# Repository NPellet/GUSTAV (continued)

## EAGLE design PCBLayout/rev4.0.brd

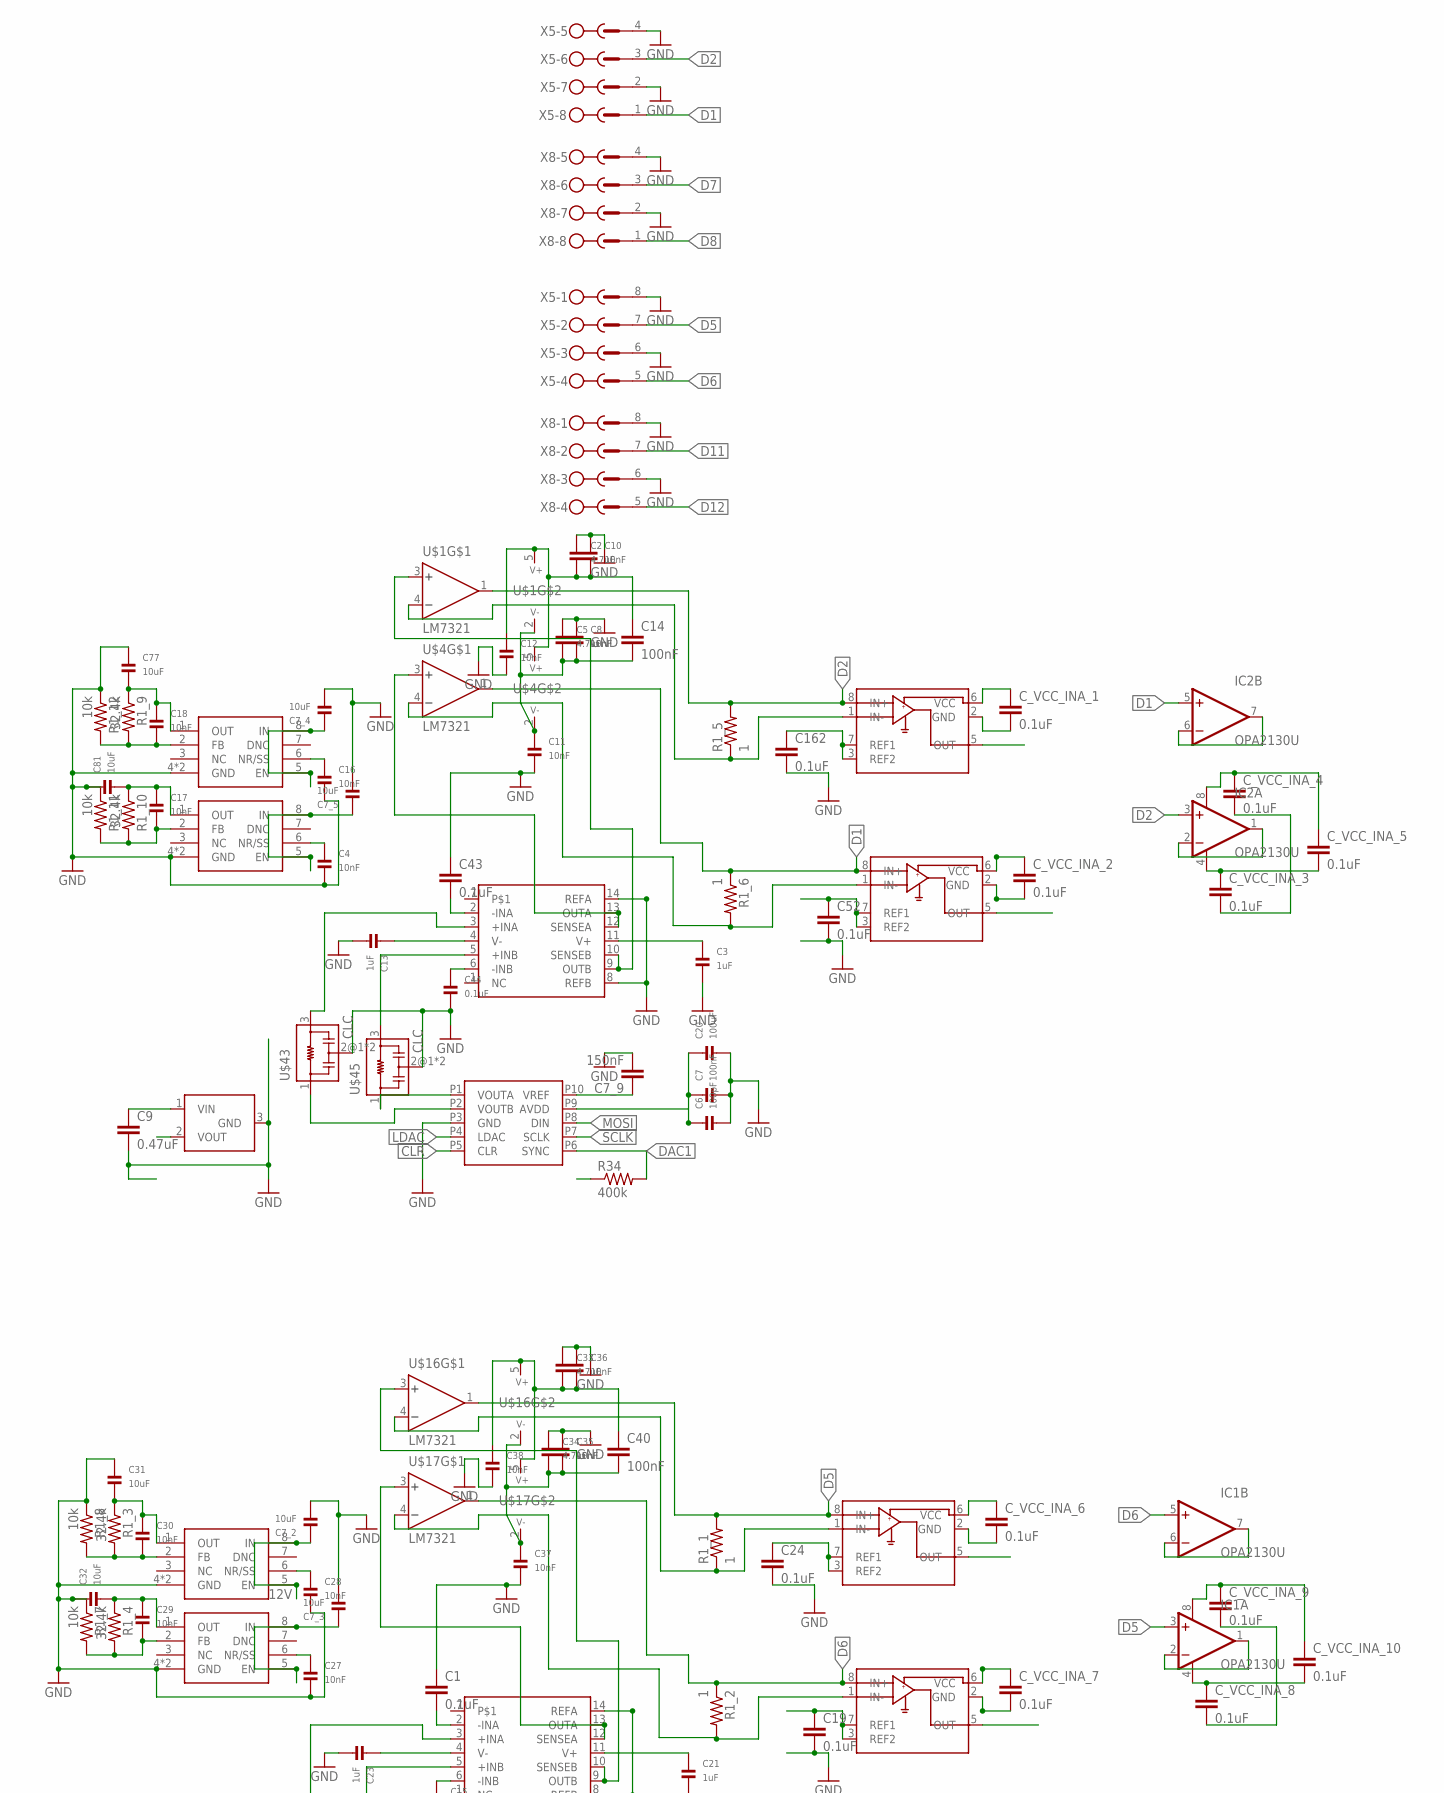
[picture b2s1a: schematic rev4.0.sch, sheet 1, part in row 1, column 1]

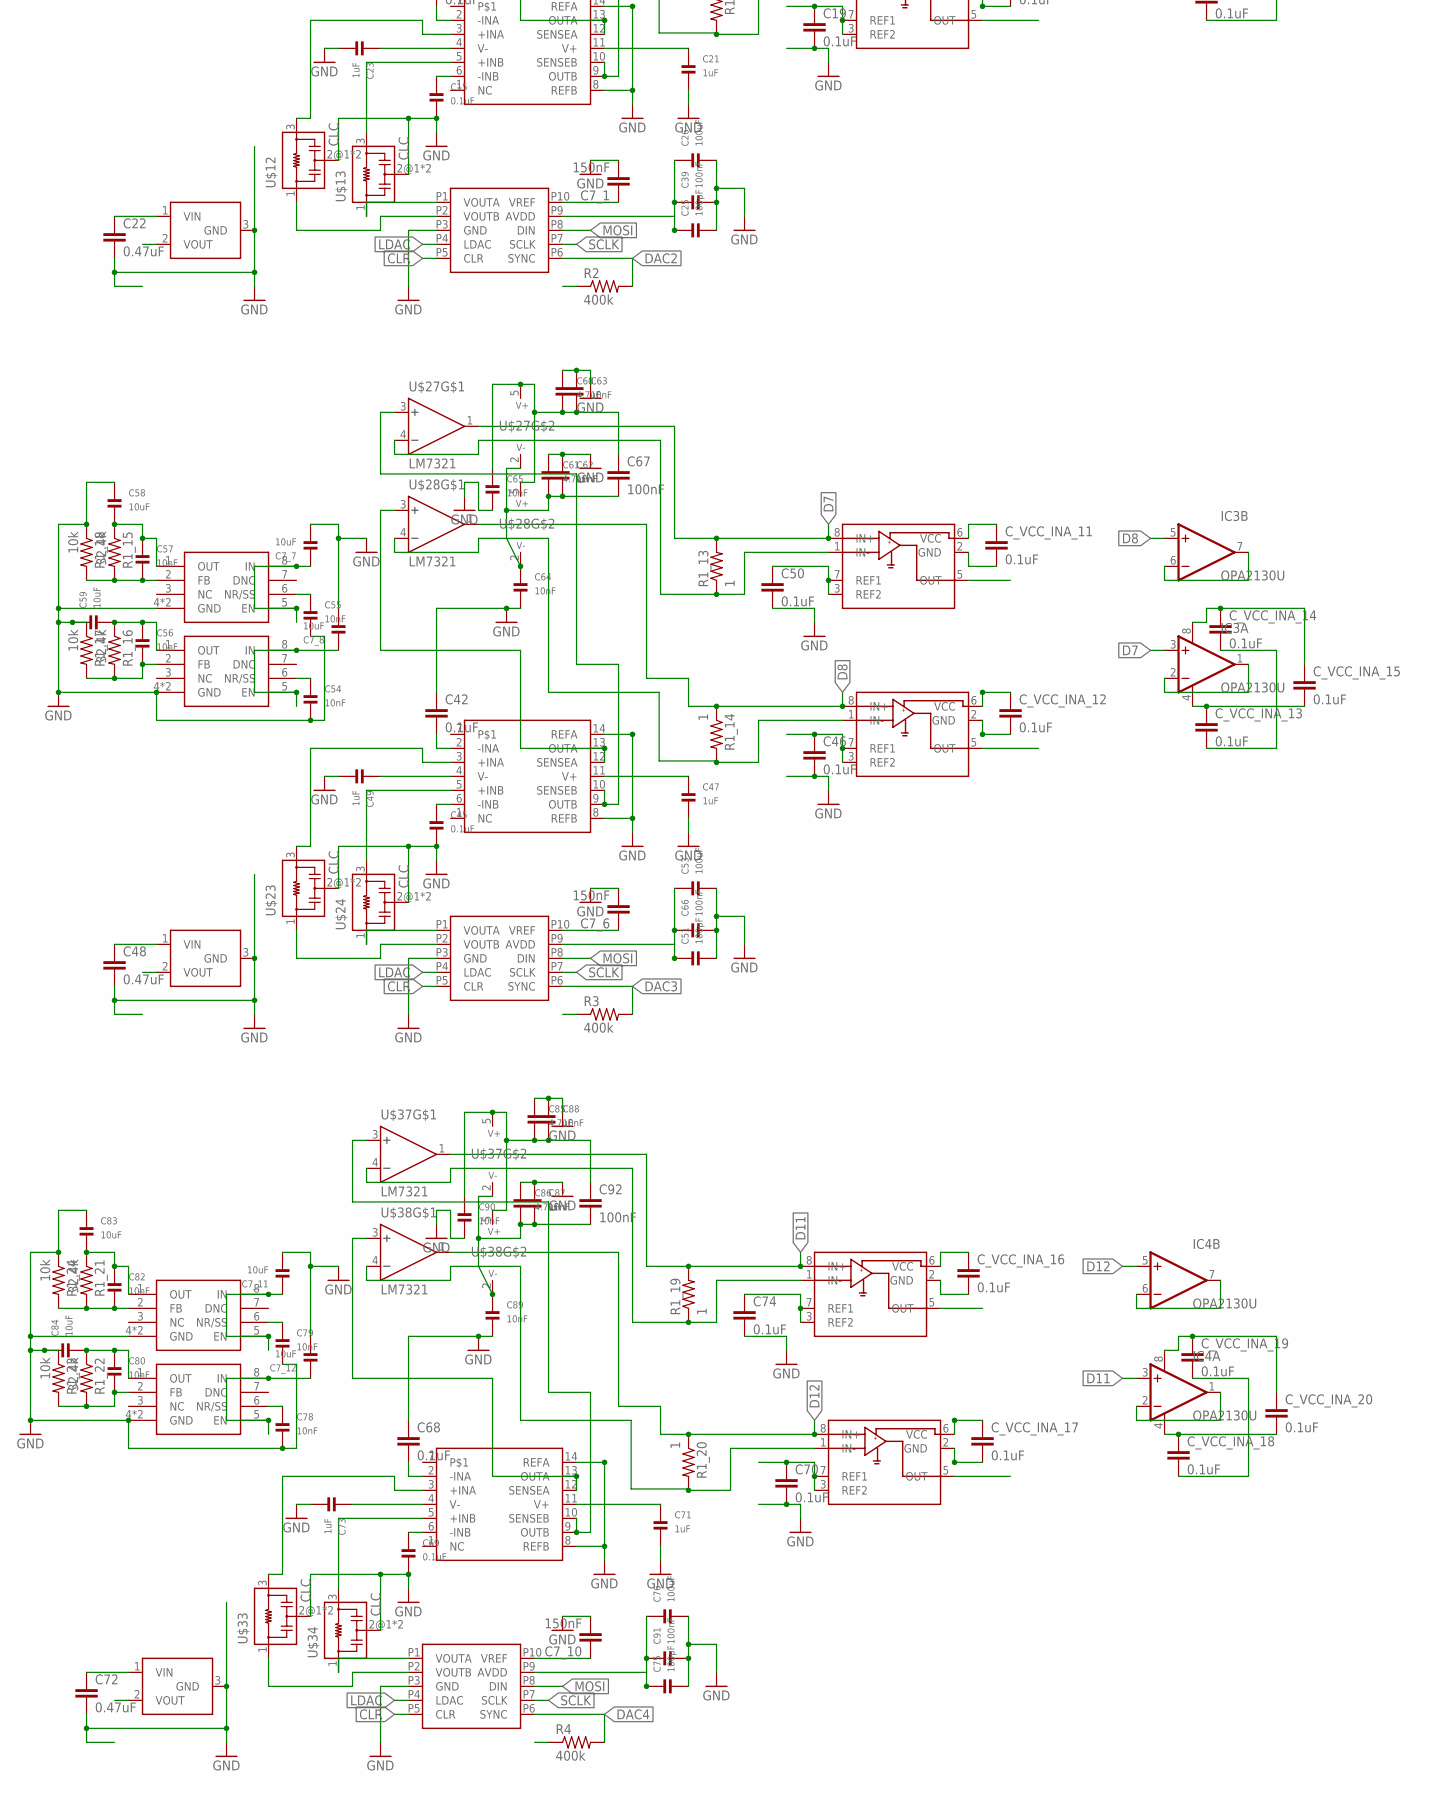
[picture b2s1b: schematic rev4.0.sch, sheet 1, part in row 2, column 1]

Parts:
C1, C19, C24, C42, C43, C46, C50, C52, C68, C70, C74, C162: 0.1uF; 0402-CAP
C2, C5, C33, C34, C60, C61, C85, C86: 4.7uF; 0805
C3, C13, C21, C23, C47, C49, C71, C73: 1uF; 0402
C4, C8, C10, C11, C12, C16, C17, C18, C27, C28, C29, C30, C35, C36, C37, C38, C54, C55, C56, C57, C62, C63, C64, C65, C78, C79, C80, C82, C87, C88, C89, C90: 10nF; 0402
C6, C25, C51, C75: 100pF; 0402
C7, C39, C66, C91: 100nF; 0402
C7_1, C7_6, C7_9, C7_10: 150nF; 0402-CAP
C7_2, C7_3, C7_4, C7_5, C7_7, C7_8, C7_11, C7_12, C31, C32, C58, C59, C77, C81, C83, C84: 10uF; 0805
C9, C22, C48, C72: 0.47uF; 0402-CAP
C14, C40, C67, C92: 100nF; 0402-CAP
C15, C44, C45, C69: 0.1uF; 0402
C20, C26, C53, C76: 100uF; 1206
C_VCC_INA_1, C_VCC_INA_2, C_VCC_INA_3, C_VCC_INA_4, C_VCC_INA_5, C_VCC_INA_6, C_VCC_INA_7, C_VCC_INA_8, C_VCC_INA_9, C_VCC_INA_10, C_VCC_INA_11, C_VCC_INA_12, C_VCC_INA_13, C_VCC_INA_14, C_VCC_INA_15, C_VCC_INA_16, C_VCC_INA_17, C_VCC_INA_18, C_VCC_INA_19, C_VCC_INA_20: 0.1uF; 0402-CAP
IC1, IC2, IC3, IC4: OPA2130U; SO08
R1_1, R1_2, R1_5, R1_6, R1_13, R1_14, R1_19, R1_20: 1; 0603-RES
R1_3, R1_4, R1_9, R1_10, R1_15, R1_16, R1_21, R1_22: 32.4k; 0603-RES
R1_7, R1_8, R1_11, R1_12, R1_17, R1_18, R1_23, R1_24: 10k; 0603-RES
R2, R3, R4, R34: 400k; 0603-RES
REF1, REF2, REF3, REF3040: REF3040; DBZ_R-PDSO-G3
U$1, U$4, U$16, U$17, U$27, U$28, U$37, U$38: LM7321; DCK_R-PDSO-G5
U$2, U$10, U$20, U$31: INA2132; SO-14
U$3, U$11, U$21, U$32: DAC7563; S-PDSO-G10
U$5, U$7, U$8, U$9, U$18, U$19, U$29, U$30: INA285PDSO-G8; S-PDSO-G08-NOTHERMALPAD
U$12, U$13, U$23, U$24, U$33, U$34, U$43, U$45: CLC; NFM21C
U$14, U$15, U$25, U$26, U$35, U$36, U$53, U$54: TPS7A30; S-PDSO-G08
X5, X8: MSTBV8

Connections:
12V: C7_2.1, C7_4.1, C7_7.1, C7_11.1, U$14.5 (EN), U$14.8 (IN), U$25.5 (EN), U$25.8 (IN), U$35.5 (EN), U$35.8 (IN), U$53.5 (EN), U$53.8 (IN); also elsewhere on the board
-9V: C7_3.1, C7_5.1, C7_8.1, C7_12.1, U$15.5 (EN), U$15.8 (IN), U$26.5 (EN), U$26.8 (IN), U$36.5 (EN), U$36.8 (IN), U$54.5 (EN), U$54.8 (IN); also elsewhere on the board
CLR: U$3.P5 (CLR), U$11.P5 (CLR), U$21.P5 (CLR), U$32.P5 (CLR); also elsewhere on the board
D1: IC2.5 (+IN), R1_6.1, U$4.1 (OUT), U$8.8 (IN+), X5.1
D2: IC2.3 (+IN), R1_5.2, U$1.1 (OUT), U$7.8 (IN+), X5.3
D5: IC1.3 (+IN), R1_1.2, U$5.8 (IN+), U$16.1 (OUT), X5.7
D6: IC1.5 (+IN), R1_2.1, U$9.8 (IN+), U$17.1 (OUT), X5.5
D7: IC3.3 (+IN), R1_13.2, U$18.8 (IN+), U$27.1 (OUT), X8.3
D8: IC3.5 (+IN), R1_14.1, U$19.8 (IN+), U$28.1 (OUT), X8.1
D11: IC4.3 (+IN), R1_19.2, U$29.8 (IN+), U$37.1 (OUT), X8.7
D12: IC4.5 (+IN), R1_20.1, U$30.8 (IN+), U$38.1 (OUT), X8.5
DAC1: R34.2, U$3.P6 (SYNC); also elsewhere on the board
DAC2: R2.2, U$11.P6 (SYNC); also elsewhere on the board
DAC3: R3.2, U$21.P6 (SYNC); also elsewhere on the board
DAC4: R4.2, U$32.P6 (SYNC); also elsewhere on the board
GND: C1.1, C2.1, C3.2, C4.2, C5.1, C6.2, C7.2, C7_1.2, C7_2.2, C7_3.2, C7_4.2, C7_5.2, C7_6.2, C7_7.2, C7_8.2, C7_9.2, C7_10.2, C7_11.2, C7_12.2, C8.1, C9.2, C10.1, C11.2, C12.2, C13.2, C15.2, C16.2, C19.2, C20.2, C21.2, C22.2, C23.2, C24.2, C25.2, C26.2, C27.2, C28.2, C31.1, C32.1, C33.1, C34.1, C35.1, C36.1, C37.2, C38.2, C39.2, C42.1, C43.1, C44.2, C45.2, C46.2, C47.2, C48.2, C49.2, C50.2, C51.2, C52.2, C53.2, C54.2, C55.2, C58.1, C59.1, C60.1, C61.1, C62.1, C63.1, C64.2, C65.2, C66.2, C68.1, C69.2, C70.2, C71.2, C72.2, C73.2, C74.2, C75.2, C76.2, C77.1, C78.2, C79.2, C81.1, C83.1, C84.1, C85.1, C86.1, C87.1, C88.1, C89.2, C90.2, C91.2, C162.2, C_VCC_INA_1.2, C_VCC_INA_2.2, C_VCC_INA_3.2, C_VCC_INA_4.2, C_VCC_INA_6.2, C_VCC_INA_7.2, C_VCC_INA_8.2, C_VCC_INA_9.2, C_VCC_INA_11.2, C_VCC_INA_12.2, C_VCC_INA_13.2, C_VCC_INA_14.2, C_VCC_INA_16.2, C_VCC_INA_17.2, C_VCC_INA_18.2, C_VCC_INA_19.2, R1_7.1, R1_8.1, R1_11.1, R1_12.1, R1_17.1, R1_18.1, R1_23.1, R1_24.1, REF1.3 (GND), REF2.3 (GND), REF3.3 (GND), REF3040.3 (GND), U$2.8 (REFB), U$2.14 (REFA), U$3.P3 (GND), U$5.2 (GND), U$7.2 (GND), U$8.2 (GND), U$9.2 (GND), U$10.8 (REFB), U$10.14 (REFA), U$11.P3 (GND), U$12.2@1 (2), U$12.2@2 (2), U$13.2@1 (2), U$13.2@2 (2), U$14.4 (GND), U$14.TH (GND), U$15.4 (GND), U$15.TH (GND), U$18.2 (GND), U$19.2 (GND), U$20.8 (REFB), U$20.14 (REFA), U$21.P3 (GND), U$23.2@1 (2), U$23.2@2 (2), U$24.2@1 (2), U$24.2@2 (2), U$25.4 (GND), U$25.TH (GND), U$26.4 (GND), U$26.TH (GND), U$29.2 (GND), U$30.2 (GND), U$31.8 (REFB), U$31.14 (REFA), U$32.P3 (GND), U$33.2@1 (2), U$33.2@2 (2), U$34.2@1 (2), U$34.2@2 (2), U$35.4 (GND), U$35.TH (GND), U$36.4 (GND), U$36.TH (GND), U$43.2@1 (2), U$43.2@2 (2), U$45.2@1 (2), U$45.2@2 (2), U$53.4 (GND), U$53.TH (GND), U$54.4 (GND), U$54.TH (GND), X5.2, X5.4, X5.6, X5.8, X8.2, X8.4, X8.6, X8.8; also elsewhere on the board
LDAC: U$3.P4 (LDAC), U$11.P4 (LDAC), U$21.P4 (LDAC), U$32.P4 (LDAC); also elsewhere on the board
MOSI: U$3.P8 (DIN), U$11.P8 (DIN), U$21.P8 (DIN), U$32.P8 (DIN); also elsewhere on the board
MUX1: IC2.6 (-IN), IC2.7 (OUT); also elsewhere on the board
MUX2: IC2.1 (OUT), IC2.2 (-IN); also elsewhere on the board
MUX3: IC1.6 (-IN), IC1.7 (OUT); also elsewhere on the board
MUX4: IC1.1 (OUT), IC1.2 (-IN); also elsewhere on the board
MUX5: IC3.6 (-IN), IC3.7 (OUT); also elsewhere on the board
MUX6: IC3.1 (OUT), IC3.2 (-IN); also elsewhere on the board
MUX7: IC4.6 (-IN), IC4.7 (OUT); also elsewhere on the board
MUX8: IC4.1 (OUT), IC4.2 (-IN); also elsewhere on the board
MUX9: U$7.5 (OUT); also elsewhere on the board
MUX10: U$8.5 (OUT); also elsewhere on the board
MUX11: U$5.5 (OUT); also elsewhere on the board
MUX12: U$9.5 (OUT); also elsewhere on the board
MUX13: U$18.5 (OUT); also elsewhere on the board
MUX14: U$19.5 (OUT); also elsewhere on the board
MUX15: U$29.5 (OUT); also elsewhere on the board
MUX16: U$30.5 (OUT); also elsewhere on the board
unnamed: U$3.P1 (VOUTA), U$45.1
unnamed: U$1.3 (+), U$2.9 (OUTB), U$2.10 (SENSEB)
unnamed: U$3.P2 (VOUTB), U$43.1
unnamed: U$2.12 (SENSEA), U$2.13 (OUTA), U$4.3 (+)
unnamed: U$10.9 (OUTB), U$10.10 (SENSEB), U$16.3 (+)
unnamed: U$10.12 (SENSEA), U$10.13 (OUTA), U$17.3 (+)
unnamed: U$10.5 (+INB), U$13.3
unnamed: C27.1, U$15.6 (NR/SS)
unnamed: C28.1, U$14.6 (NR/SS)
unnamed: C29.2, R1_4.2, R1_7.2, U$15.2 (FB)
unnamed: C30.2, R1_3.2, R1_8.2, U$14.2 (FB)
unnamed: U$11.P1 (VOUTA), U$13.1
unnamed: U$11.P2 (VOUTB), U$12.1
unnamed: U$20.9 (OUTB), U$20.10 (SENSEB), U$27.3 (+)
unnamed: U$20.12 (SENSEA), U$20.13 (OUTA), U$28.3 (+)
unnamed: U$20.5 (+INB), U$24.3
unnamed: C54.1, U$26.6 (NR/SS)
unnamed: C55.1, U$25.6 (NR/SS)
unnamed: C56.2, R1_16.2, R1_17.2, U$26.2 (FB)
unnamed: C57.2, R1_15.2, R1_18.2, U$25.2 (FB)
unnamed: U$21.P1 (VOUTA), U$24.1
unnamed: U$21.P2 (VOUTB), U$23.1
unnamed: U$31.9 (OUTB), U$31.10 (SENSEB), U$37.3 (+)
unnamed: U$31.12 (SENSEA), U$31.13 (OUTA), U$38.3 (+)
unnamed: U$31.5 (+INB), U$34.3
unnamed: C78.1, U$36.6 (NR/SS)
unnamed: C79.1, U$35.6 (NR/SS)
unnamed: C80.2, R1_22.2, R1_23.2, U$36.2 (FB)
unnamed: C82.2, R1_21.2, R1_24.2, U$35.2 (FB)
unnamed: U$32.P1 (VOUTA), U$34.1
unnamed: U$32.P2 (VOUTB), U$33.1
unnamed: U$2.5 (+INB), U$45.3
unnamed: C4.1, U$54.6 (NR/SS)
unnamed: C16.1, U$53.6 (NR/SS)
unnamed: C17.2, R1_10.2, R1_11.2, U$54.2 (FB)
unnamed: C18.2, R1_9.2, R1_12.2, U$53.2 (FB)
OUTPUTA: R1_6.2, U$4.4 (-), U$8.1 (IN-)
OUTPUTA1: R1_2.2, U$9.1 (IN-), U$17.4 (-)
OUTPUTA2: R1_14.2, U$19.1 (IN-), U$28.4 (-)
OUTPUTA3: R1_20.2, U$30.1 (IN-), U$38.4 (-)
OUTPUTB: R1_5.1, U$1.4 (-), U$7.1 (IN-)
OUTPUTB1: R1_1.1, U$5.1 (IN-), U$16.4 (-)
OUTPUTB2: R1_13.1, U$18.1 (IN-), U$27.4 (-)
OUTPUTB3: R1_19.1, U$29.1 (IN-), U$37.4 (-)
REF2: C1.2, C15.1, C19.1, C24.1, C42.2, C43.2, C44.1, C45.1, C46.1, C50.1, C52.1, C68.2, C69.1, C70.1, C74.1, C162.1, U$2.2 (-INA), U$2.6 (-INB), U$5.3 (REF2), U$5.7 (REF1), U$7.3 (REF2), U$7.7 (REF1), U$8.3 (REF2), U$8.7 (REF1), U$9.3 (REF2), U$9.7 (REF1), U$10.2 (-INA), U$10.6 (-INB), U$18.3 (REF2), U$18.7 (REF1), U$19.3 (REF2), U$19.7 (REF1), U$20.2 (-INA), U$20.6 (-INB), U$29.3 (REF2), U$29.7 (REF1), U$30.3 (REF2), U$30.7 (REF1), U$31.2 (-INA), U$31.6 (-INB); also elsewhere on the board
REF3: C7_1.1, REF1.2 (VOUT), U$11.P10 (VREF)
REF4: C7_9.1, REF3040.2 (VOUT), U$3.P10 (VREF)
REF6: C7_6.1, REF2.2 (VOUT), U$21.P10 (VREF)
REF8: C7_10.1, REF3.2 (VOUT), U$32.P10 (VREF)
SCLK: U$3.P7 (SCLK), U$11.P7 (SCLK), U$21.P7 (SCLK), U$32.P7 (SCLK); also elsewhere on the board
VOUTA: U$2.3 (+INA), U$43.3
VOUTA1: U$10.3 (+INA), U$12.3
VOUTA2: U$20.3 (+INA), U$23.3
VOUTA3: U$31.3 (+INA), U$33.3
VREF: C2.2, C3.1, C6.1, C7.1, C9.1, C10.2, C12.1, C14.1, C18.1, C20.1, C77.2, C_VCC_INA_1.1, C_VCC_INA_2.1, C_VCC_INA_4.1, C_VCC_INA_5.1, IC2.8 (V+), R1_9.1, R34.1, REF3040.1 (VIN), U$1.5 (V+), U$2.11 (V+), U$3.P9 (AVDD), U$4.5 (V+), U$7.6 (VCC), U$8.6 (VCC), U$53.1 (OUT)
VREF1: C21.1, C22.1, C25.1, C26.1, C30.1, C31.2, C33.2, C36.2, C38.1, C39.1, C40.1, C_VCC_INA_6.1, C_VCC_INA_7.1, C_VCC_INA_9.1, C_VCC_INA_10.1, IC1.8 (V+), R1_3.1, R2.1, REF1.1 (VIN), U$5.6 (VCC), U$9.6 (VCC), U$10.11 (V+), U$11.P9 (AVDD), U$14.1 (OUT), U$16.5 (V+), U$17.5 (V+)
VREF2: C47.1, C48.1, C51.1, C53.1, C57.1, C58.2, C60.2, C63.2, C65.1, C66.1, C67.1, C_VCC_INA_11.1, C_VCC_INA_12.1, C_VCC_INA_14.1, C_VCC_INA_15.1, IC3.8 (V+), R1_15.1, R3.1, REF2.1 (VIN), U$18.6 (VCC), U$19.6 (VCC), U$20.11 (V+), U$21.P9 (AVDD), U$25.1 (OUT), U$27.5 (V+), U$28.5 (V+)
VREF3: C71.1, C72.1, C75.1, C76.1, C82.1, C83.2, C85.2, C88.2, C90.1, C91.1, C92.1, C_VCC_INA_16.1, C_VCC_INA_17.1, C_VCC_INA_19.1, C_VCC_INA_20.1, IC4.8 (V+), R1_21.1, R4.1, REF3.1 (VIN), U$29.6 (VCC), U$30.6 (VCC), U$31.11 (V+), U$32.P9 (AVDD), U$35.1 (OUT), U$37.5 (V+), U$38.5 (V+)
VREF-: C5.2, C8.2, C11.1, C13.1, C14.2, C17.1, C81.2, C_VCC_INA_3.1, C_VCC_INA_5.2, IC2.4 (V-), R1_10.1, U$1.2 (V-), U$2.4 (V-), U$4.2 (V-), U$54.1 (OUT)
VREF-1: C23.1, C29.1, C32.2, C34.2, C35.2, C37.1, C40.2, C_VCC_INA_8.1, C_VCC_INA_10.2, IC1.4 (V-), R1_4.1, U$10.4 (V-), U$15.1 (OUT), U$16.2 (V-), U$17.2 (V-)
VREF-2: C49.1, C56.1, C59.2, C61.2, C62.2, C64.1, C67.2, C_VCC_INA_13.1, C_VCC_INA_15.2, IC3.4 (V-), R1_16.1, U$20.4 (V-), U$26.1 (OUT), U$27.2 (V-), U$28.2 (V-)
VREF-3: C73.1, C80.1, C84.2, C86.2, C87.2, C89.1, C92.2, C_VCC_INA_18.1, C_VCC_INA_20.2, IC4.4 (V-), R1_22.1, U$31.4 (V-), U$36.1 (OUT), U$37.2 (V-), U$38.2 (V-)

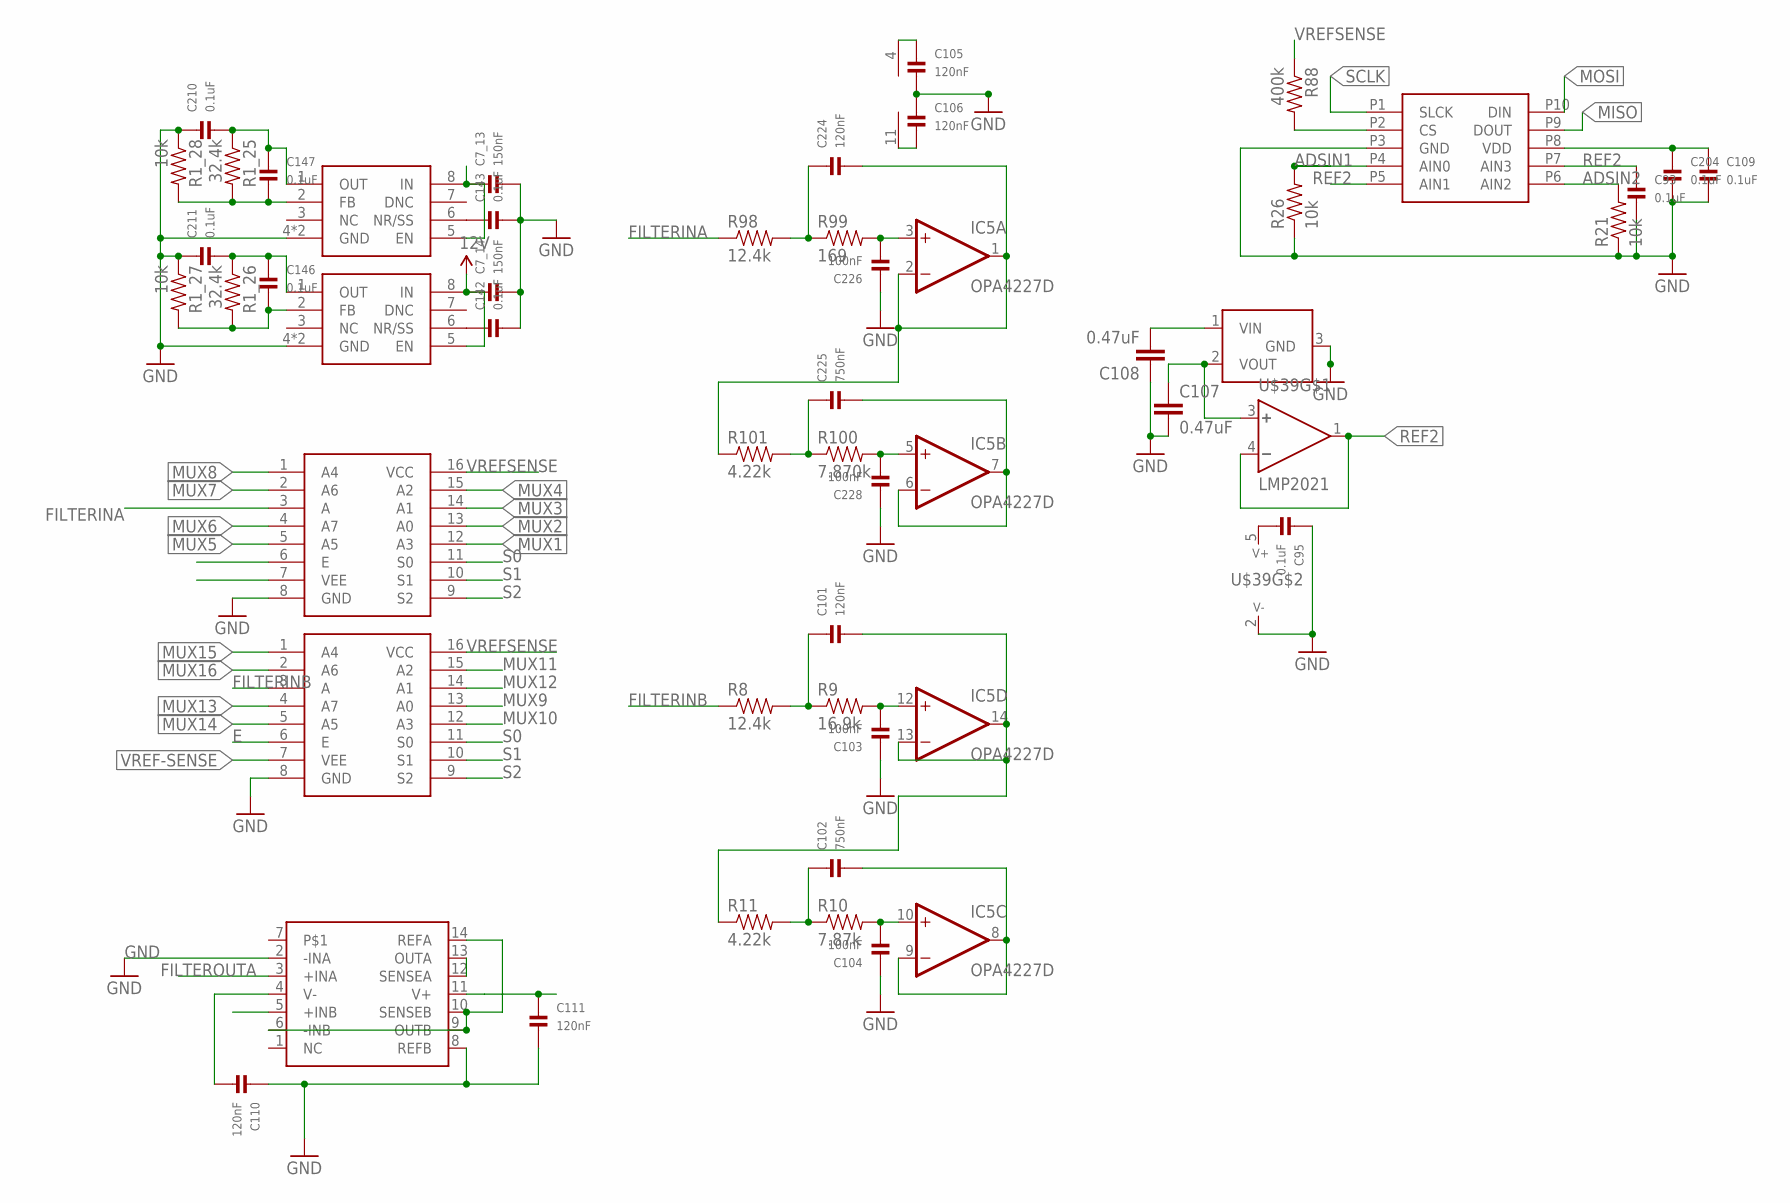
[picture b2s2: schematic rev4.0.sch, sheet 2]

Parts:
C7_13, C7_14: 150nF; 0603-MINI
C93, C95, C109, C142, C143, C146, C147, C204: 0.1uF; 0402
C101, C105, C106, C110, C111, C224: 120nF; 0402
C102, C225: 750nF; 0402
C103, C104, C226, C228: 100nF; 0402
C107, C108: 0.47uF; 0402-CAP
C210, C211: 0.1uF; 0603-MINI
IC5: OPA4227D; SO14
R1_25, R1_26: 32.4k; 0603-RES
R1_27, R1_28: 10k; 0603-RES
R8, R98: 12.4k; 0603-RES
R9: 16.9k; 0603-RES
R10: 7.87k; 0603-RES
R11, R101: 4.22k; 0603-RES
R21, R26: 10k; 0603
R88: 400k; 0603-RES
R99: 169; 0603-RES
R100: 7.870k; 0603-RES
REF7: REF3020; DBZ_R-PDSO-G3
U$6, U$57: CD54HC4051; PW_R-PDSO-G16
U$39: LMP2021; SOT23-DBV
U$40: ADS1018; S-PDSO-G10
U$48, U$49: TPS7A30; S-PDSO-G08
U$58: INA2132; SO-14

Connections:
12V: C7_14.1, U$49.5 (EN), U$49.8 (IN); also elsewhere on the board
-9V: C7_13.1, U$48.5 (EN), U$48.8 (IN); also elsewhere on the board
ADCCS: R88.2, U$40.P2 (CS); also elsewhere on the board
ADSIN1: C102.2, IC5.8 (OUT), IC5.9 (-IN), R26.2, U$40.P4 (AIN0)
ADSIN2: R21.2, U$40.P6 (AIN2), U$58.12 (SENSEA), U$58.13 (OUTA)
E: U$6.6 (E), U$57.6 (E); also elsewhere on the board
FILTERINA: R98.1, U$6.3 (A)
FILTERINB: R8.1, U$57.3 (A)
FILTEROUTA: C225.2, IC5.6 (-IN), IC5.7 (OUT), U$58.3 (+INA)
GND: C7_13.2, C7_14.2, C93.2, C95.1, C103.1, C104.1, C105.2, C106.1, C107.2, C108.1, C109.2, C110.1, C111.2, C142.2, C143.2, C204.2, C210.1, C211.1, C226.1, C228.1, R1_27.1, R1_28.1, R21.1, R26.1, REF7.3 (GND), U$6.8 (GND), U$39.2 (V-), U$40.P3 (GND), U$48.4 (GND), U$48.TH (GND), U$49.4 (GND), U$49.TH (GND), U$57.8 (GND), U$58.2 (-INA), U$58.8 (REFB); also elsewhere on the board
MISO: U$40.P9 (DOUT); also elsewhere on the board
MOSI: U$40.P10 (DIN); also elsewhere on the board
MUX1: U$6.12 (A3); also elsewhere on the board
MUX2: U$6.13 (A0); also elsewhere on the board
MUX3: U$6.14 (A1); also elsewhere on the board
MUX4: U$6.15 (A2); also elsewhere on the board
MUX5: U$6.5 (A5); also elsewhere on the board
MUX6: U$6.4 (A7); also elsewhere on the board
MUX7: U$6.2 (A6); also elsewhere on the board
MUX8: U$6.1 (A4); also elsewhere on the board
MUX9: U$57.13 (A0); also elsewhere on the board
MUX10: U$57.12 (A3); also elsewhere on the board
MUX11: U$57.15 (A2); also elsewhere on the board
MUX12: U$57.14 (A1); also elsewhere on the board
MUX13: U$57.4 (A7); also elsewhere on the board
MUX14: U$57.5 (A5); also elsewhere on the board
MUX15: U$57.1 (A4); also elsewhere on the board
MUX16: U$57.2 (A6); also elsewhere on the board
unnamed: C107.1, REF7.2 (VOUT), U$39.3 (+)
unnamed: C101.2, IC5.13 (-IN), IC5.14 (OUT), R11.1
unnamed: C103.2, IC5.12 (+IN), R9.2
unnamed: C104.2, IC5.10 (+IN), R10.2
unnamed: C102.1, R10.1, R11.2
unnamed: U$58.6 (-INB), U$58.9 (OUTB), U$58.10 (SENSEB), U$58.14 (REFA)
unnamed: C101.1, R8.2, R9.1
unnamed: C143.1, U$48.6 (NR/SS)
unnamed: C142.1, U$49.6 (NR/SS)
unnamed: C146.2, R1_26.2, R1_27.2, U$49.2 (FB)
unnamed: C147.2, R1_25.2, R1_28.2, U$48.2 (FB)
unnamed: C226.2, IC5.3 (+IN), R99.2
unnamed: C228.2, IC5.5 (+IN), R100.2
unnamed: C225.1, R100.1, R101.2
unnamed: C224.2, IC5.1 (OUT), IC5.2 (-IN), R101.1
unnamed: C224.1, R98.2, R99.1
REF2: C93.1, U$39.1 (OUT), U$39.4 (-), U$40.P5 (AIN1), U$40.P7 (AIN3), U$58.5 (+INB); also elsewhere on the board
S0: U$6.11 (S0), U$57.11 (S0); also elsewhere on the board
S1: U$6.10 (S1), U$57.10 (S1); also elsewhere on the board
S2: U$6.9 (S2), U$57.9 (S2); also elsewhere on the board
SCLK: U$40.P1 (SLCK); also elsewhere on the board
VREF-SENSE: C106.2, C110.2, C147.1, C210.2, IC5.11 (V-), R1_25.1, U$6.7 (VEE), U$48.1 (OUT), U$57.7 (VEE), U$58.4 (V-)
VREFSENSE: C95.2, C105.1, C108.2, C109.1, C111.1, C146.1, C204.1, C211.2, IC5.4 (V+), R1_26.1, R88.1, REF7.1 (VIN), U$6.16 (VCC), U$39.5 (V+), U$40.P8 (VDD), U$49.1 (OUT), U$57.16 (VCC), U$58.11 (V+)

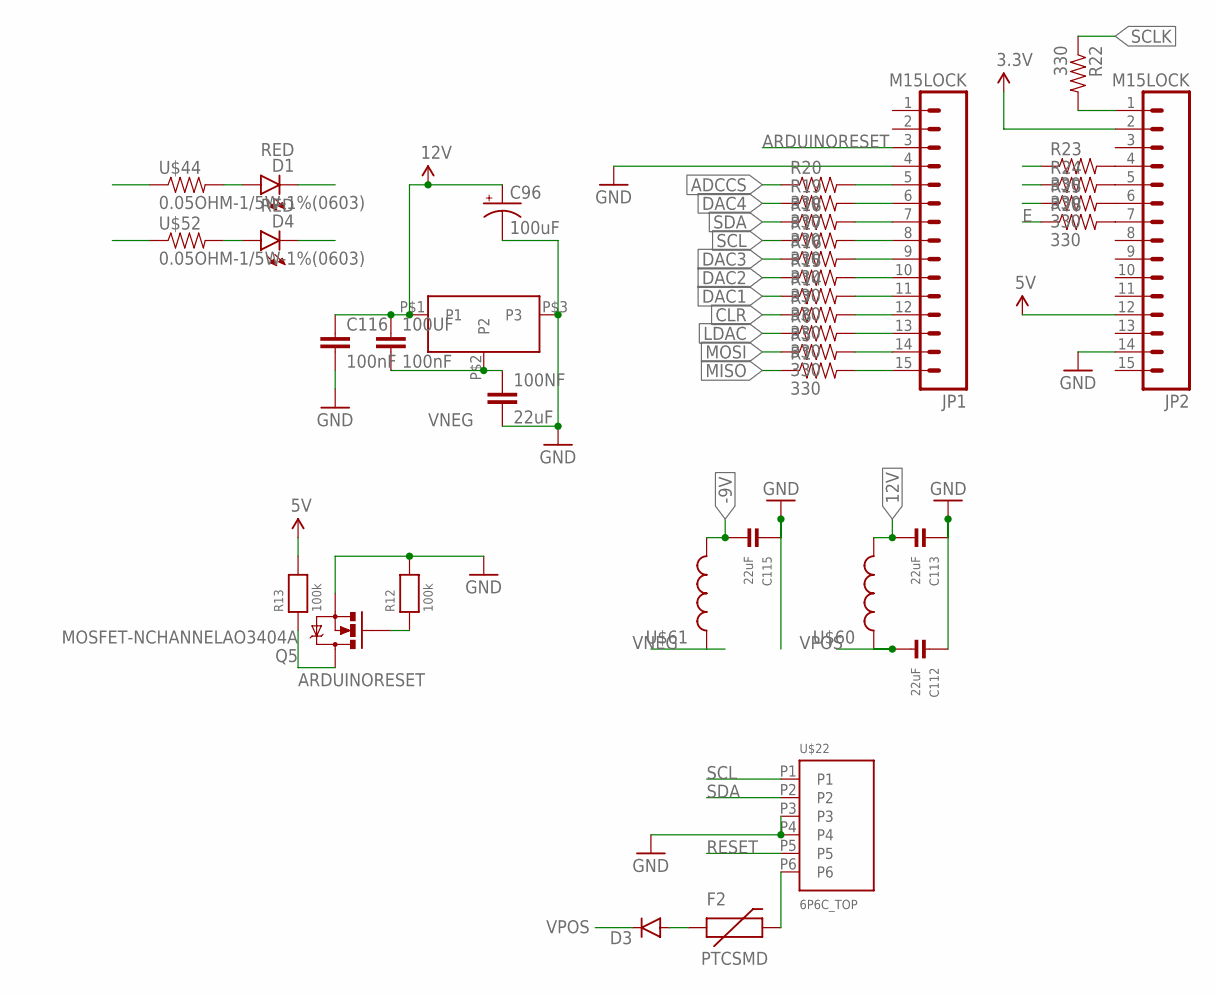
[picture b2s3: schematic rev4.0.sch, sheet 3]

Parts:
100NF: 22uF; 1206-CAP
100UF: 100nF; 1206-CAP
C96: 100uF; NIPPON_F80
C112, C113, C115: 22uF; 1206
C116: 100nF; 1206-CAP
D1, D4: RED; LED-1206
D3: DIODESMA; SMA-DIODE
F2: PTCSMD; PTC-1206
JP1, JP2: M15LOCK; 1X15_LOCK
Q5: MOSFET-NCHANNELAO3404A; SOT23-3
R1, R5, R6, R7, R14, R15, R16, R17, R18, R19, R20, R22, R23, R24, R25, R28: 330; 0603-RES
R12, R13: 100k; 0402
U$22: 6P6C_TOP
U$42: TSRN1
U$44, U$52: 0.05OHM-1/5W-1%(0603); 0603
U$60, U$61: INDUCTOR0603; 0603

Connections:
3.3V: JP2.2
5V: JP2.12, R13.2
12V: 100UF.1, C96.+, C113.2, C116.1, U$42.P$1 (P1), U$44.1, U$60.2; also elsewhere on the board
-9V: C115.2, D4.C, U$61.2; also elsewhere on the board
ADCCS: R20.1; also elsewhere on the board
ARDUINORESET: JP1.3, Q5.3 (D), R13.1
CLR: R7.1; also elsewhere on the board
D13: JP1.15, R1.2
D14: JP1.14, R5.2
D15: JP1.13, R6.2
D16: JP1.12, R7.2
D17: JP1.11, R14.2
D18: JP1.10, R15.2
D19: JP1.9, R16.2
D20: JP1.8, R17.2
D21: JP1.7, R18.2
D22: JP1.6, R19.2
D23: JP1.5, R20.2
DAC1: R14.1; also elsewhere on the board
DAC2: R15.1; also elsewhere on the board
DAC3: R16.1; also elsewhere on the board
DAC4: R19.1; also elsewhere on the board
E: R28.1; also elsewhere on the board
GND: 100NF.2, C96.-, C112.1, C113.1, C115.1, C116.2, D1.C, JP1.4, JP2.14, Q5.2 (S), R12.2, U$22.P3, U$22.P4, U$42.P$3 (P3), U$52.1; also elsewhere on the board
LDAC: R6.1; also elsewhere on the board
MISO: R1.1; also elsewhere on the board
MOSI: R5.1; also elsewhere on the board
unnamed: JP2.7, R28.2
unnamed: JP2.1, R22.2
unnamed: JP2.4, R23.2
unnamed: D1.A, U$44.2
unnamed: JP2.5, R24.2
unnamed: JP2.6, R25.2
unnamed: F2.2, U$22.P6
unnamed: D3.A, F2.1
unnamed: D4.A, U$52.2
RESET: Q5.1 (G), R12.1, U$22.P5
S0: R23.1; also elsewhere on the board
S1: R24.1; also elsewhere on the board
S2: R25.1; also elsewhere on the board
SCL: R17.1, U$22.P1
SCLK: R22.1; also elsewhere on the board
SDA: R18.1, U$22.P2
VNEG: 100NF.1, 100UF.2, U$42.P$2 (P2), U$61.1
VPOS: C112.2, D3.C, U$60.1

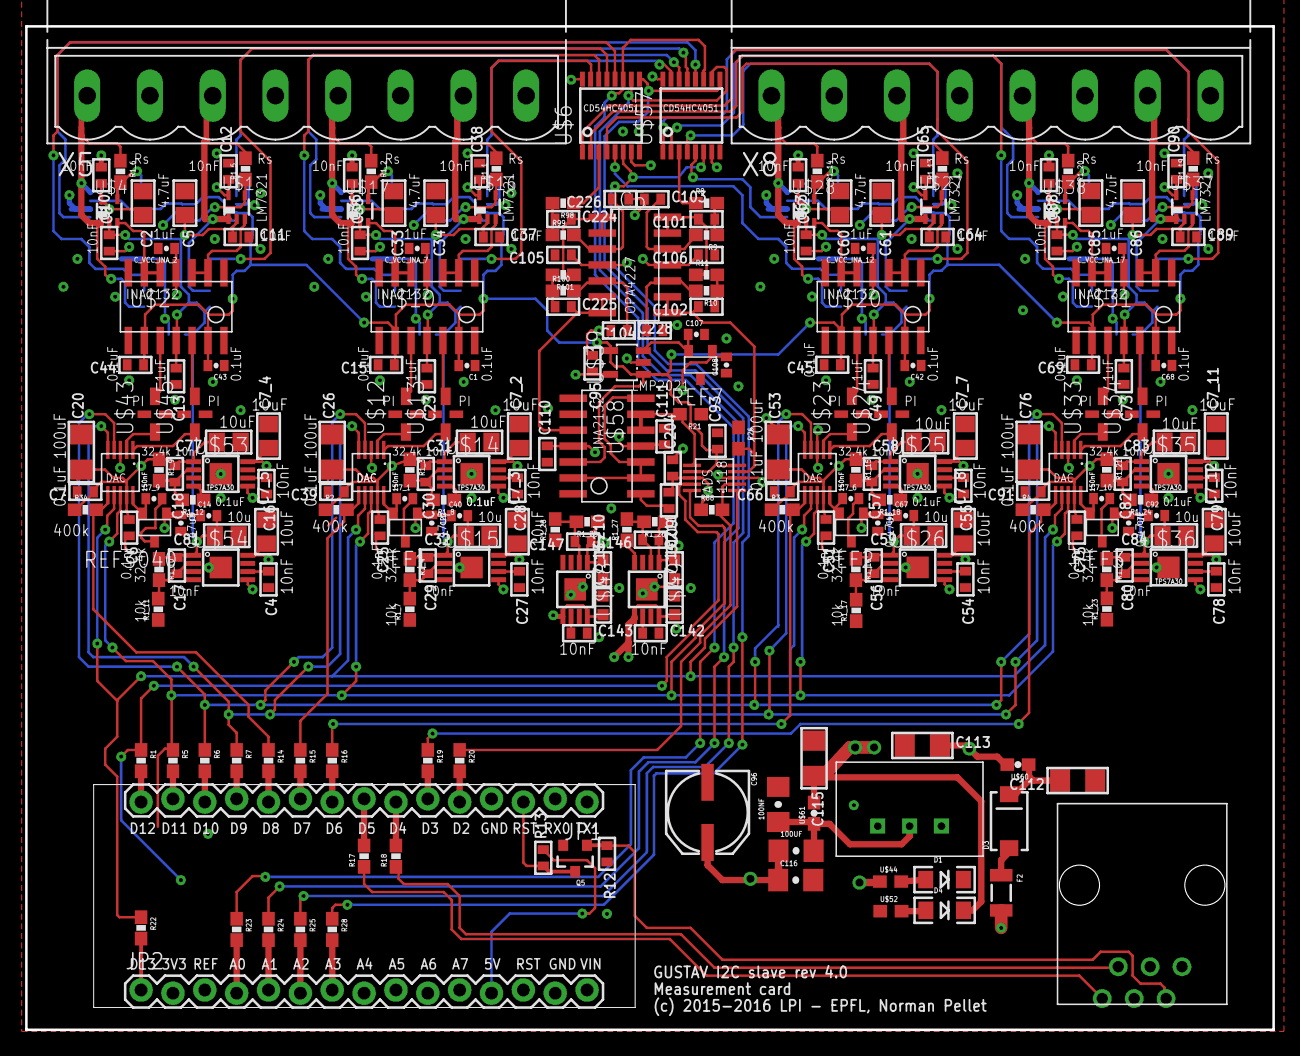
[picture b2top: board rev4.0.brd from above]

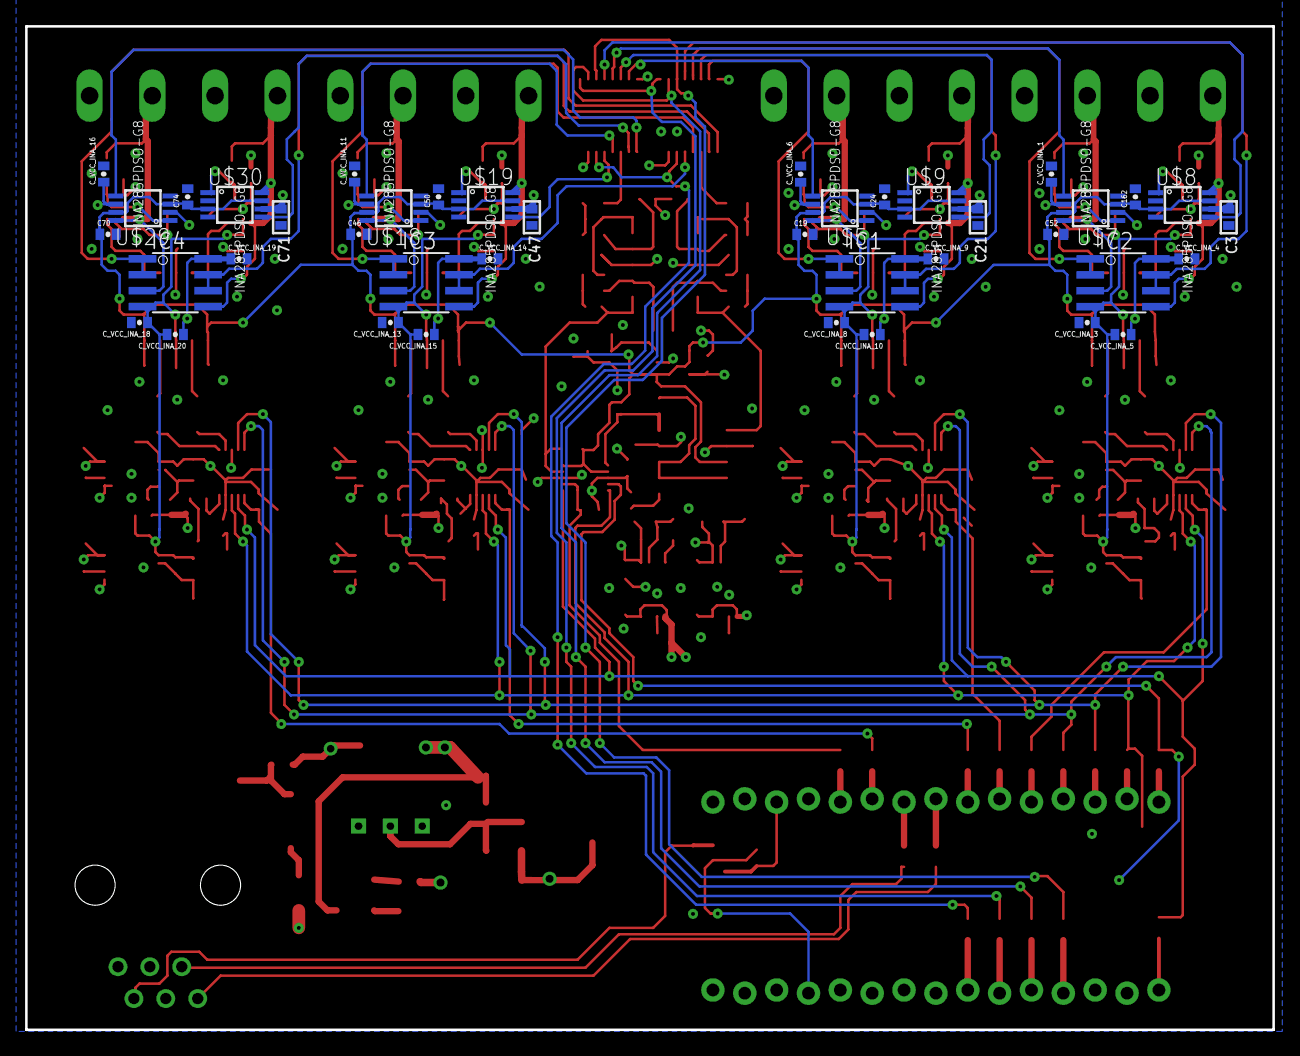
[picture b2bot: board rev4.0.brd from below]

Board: 4 copper layers, 99.5 x 80.0 mm, 290 parts (40 on the bottom side), 152 nets.
